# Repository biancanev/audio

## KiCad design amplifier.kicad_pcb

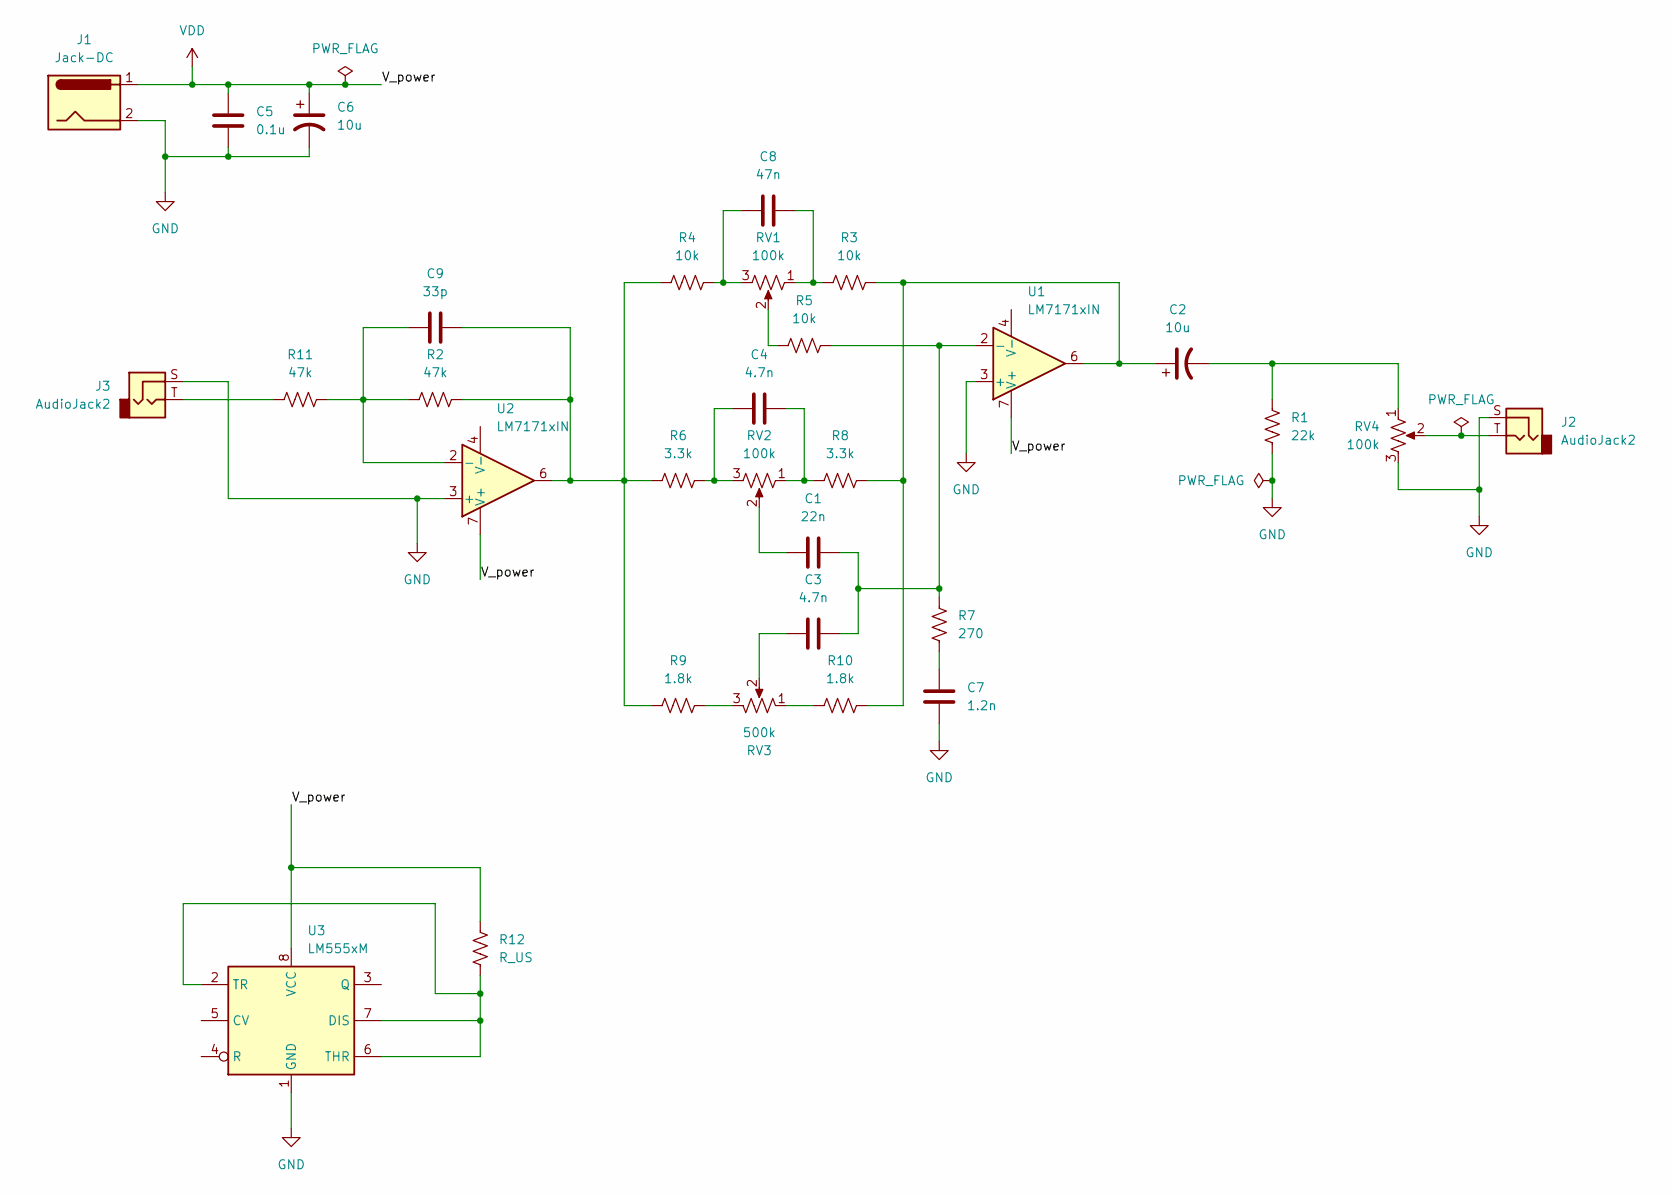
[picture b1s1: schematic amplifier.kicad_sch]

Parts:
C1: 22n; C_0603_1608Metric
C2, C6: 10u; C_0805_2012Metric
C3, C4: 4.7n; R_0603_1608Metric
C5: 0.1u; C_01005_0402Metric
C7: 1.2n; R_0402_1005Metric
C8: 47n; R_0402_1005Metric
C9: 33p; R_0402_1005Metric
J1: Jack-DC; BarrelJack_CUI_PJ-036AH-SMT_Horizontal
J2, J3: AudioJack2; Jack_6.35mm_Neutrik_NMJ4HFD3_Horizontal
R1: 22k; R_0603_1608Metric
R2, R11: 47k; R_0805_2012Metric
R3, R4, R5: 10k; R_0603_1608Metric
R6, R8: 3.3k; R_0603_1608Metric
R7: 270; R_0603_1608Metric
R9, R10: 1.8k; R_0603_1608Metric
R12: R_US
RV1, RV2, RV4: 100k; Potentiometer_ACP_CA14V-15_Vertical
RV3: 500k; Potentiometer_ACP_CA14V-15_Vertical
U1, U2: LM7171xIN; DIP-8_W7.62mm
U3: LM555xM; SOIC-8_3.9x4.9mm_P1.27mm

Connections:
GND: C5.2, C6.2, C7.2, J1.2, J2.S, J3.S, R1.2, RV4.3, U1.3 (+), U2.3 (+), U3.1 (GND)
unnamed: C1.1, RV2.2
unnamed: C2.1, R3.2, R8.2, R10.2, U1.6
unnamed: C2.2, R1.1, RV4.1
unnamed: C3.1, RV3.2
unnamed: C4.1, R6.2, RV2.3
unnamed: C4.2, R8.1, RV2.1
unnamed: C7.1, R7.2
unnamed: C8.1, R4.2, RV1.3
unnamed: C8.2, R3.1, RV1.1
unnamed: C9.2, R2.2, R4.1, R6.1, R9.1, U2.6
unnamed: J2.T, RV4.2
unnamed: J3.T, R11.1
unnamed: R5.1, RV1.2
unnamed: R9.2, RV3.3
unnamed: R10.1, RV3.1
unnamed: R12.2, U3.2 (TR), U3.6 (THR), U3.7 (DIS)
unnamed: C1.2, C3.2, R5.2, R7.1, U1.2 (-)
unnamed: C9.1, R2.1, R11.2, U2.2 (-)
VDD: C5.1, C6.1, J1.1, R12.1, U1.7 (V+), U2.7 (V+), U3.8 (VCC)

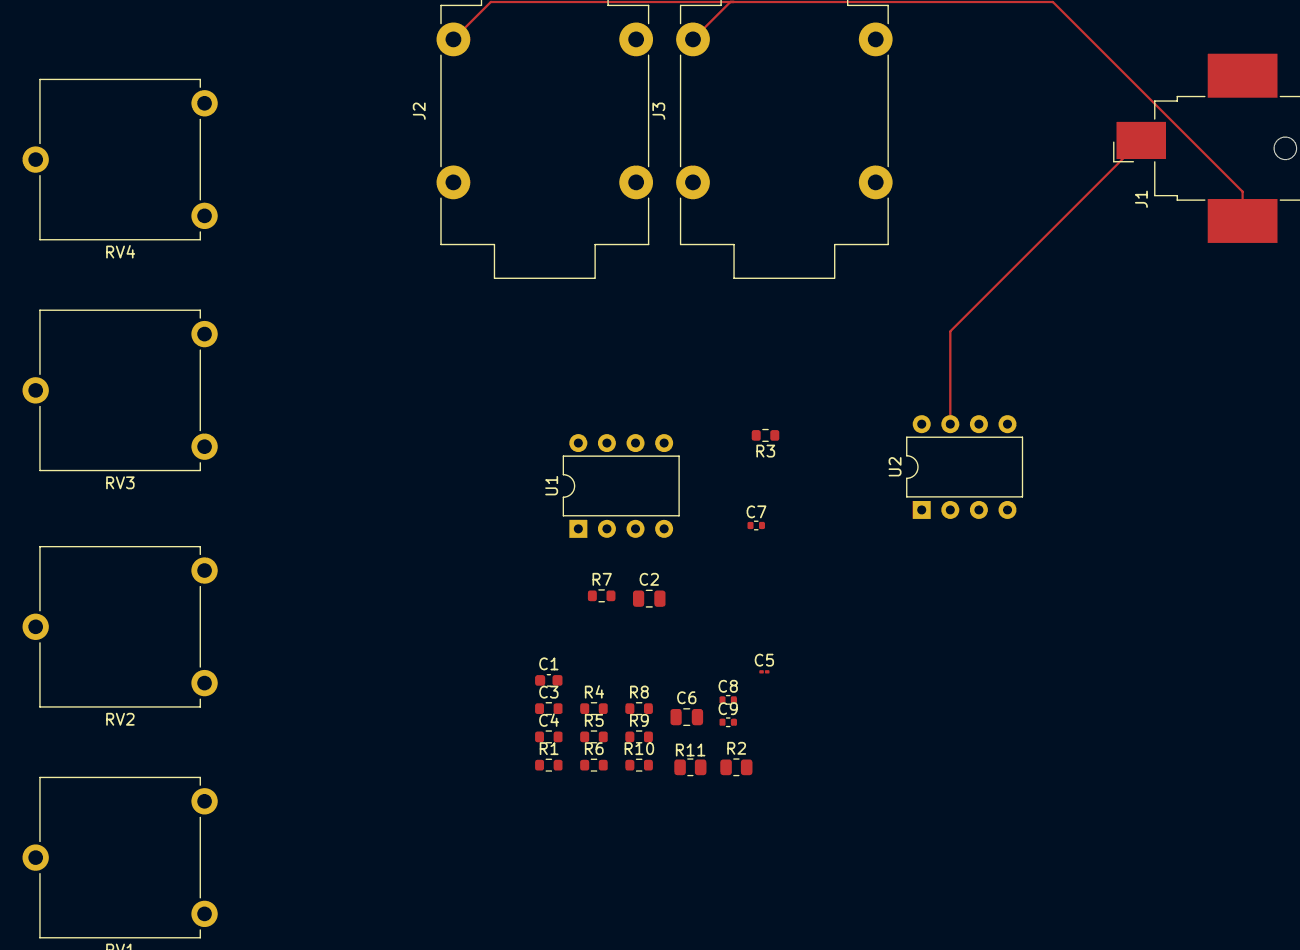
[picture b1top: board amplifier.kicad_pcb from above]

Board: 2 copper layers, 29 parts (0 on the bottom side), 19 nets.
